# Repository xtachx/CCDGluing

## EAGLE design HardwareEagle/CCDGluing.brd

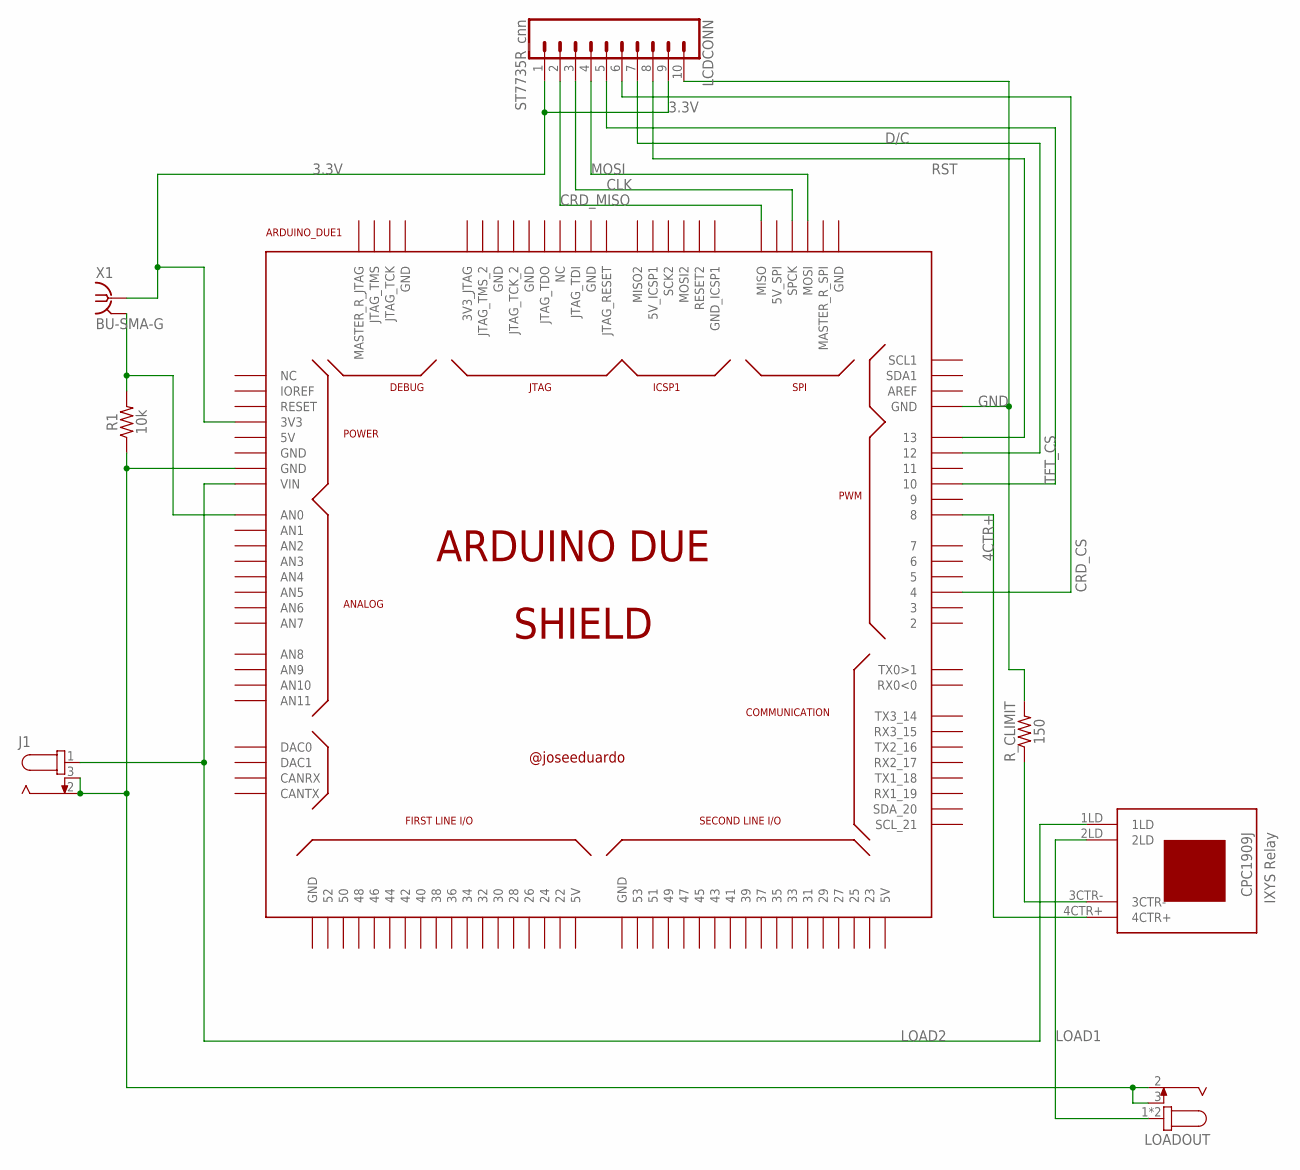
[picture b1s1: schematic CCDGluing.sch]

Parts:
ARDUINO_DUE1: ARDUINO_DUE_SHIELD
J1: 694106105102; 69410X105102
K1: CPC1909J
LCDCONN: ST7735R_cnn; 1X10
LOADOUT: 694103107102; 69410X107102
R1: 10k; 0603
R_CLIMIT: 150; 0603
X1: BU-SMA-G

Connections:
3.3V: ARDUINO_DUE1.3V3, LCDCONN.1, LCDCONN.9, X1.1
4CTR+: ARDUINO_DUE1.8, K1.4CTR+
CLK: ARDUINO_DUE1.SPCK, LCDCONN.3
CRD_CS: ARDUINO_DUE1.4, LCDCONN.6
CRD_MISO: ARDUINO_DUE1.MISO, LCDCONN.2
D/C: ARDUINO_DUE1.12, LCDCONN.7
GND: ARDUINO_DUE1.GND_4 (GND), LCDCONN.10, R_CLIMIT.2
LOAD1: K1.2LD, LOADOUT.1, LOADOUT.A1 (1)
LOAD2: ARDUINO_DUE1.VIN, J1.1, K1.1LD
LOAD_GND: ARDUINO_DUE1.GND_1 (GND), J1.2, J1.3, LOADOUT.2, LOADOUT.3, R1.1
MOSI: ARDUINO_DUE1.MOSI, LCDCONN.4
unnamed: K1.3CTR-, R_CLIMIT.1
unnamed: ARDUINO_DUE1.A0 (AN0), R1.2, X1.2, X1.3 (2), X1.4 (2), X1.5 (2)
RST: ARDUINO_DUE1.13, LCDCONN.8
TFT_CS: ARDUINO_DUE1.10, LCDCONN.5

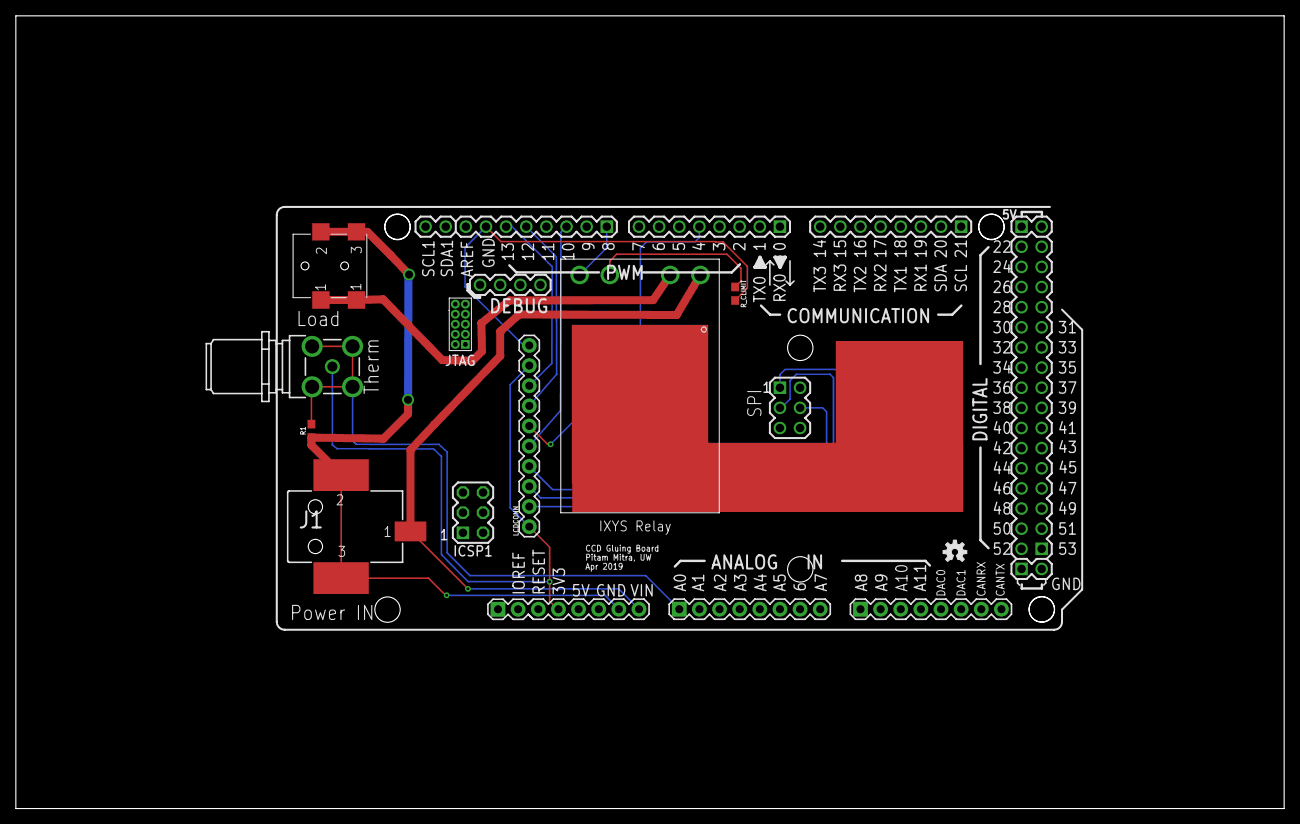
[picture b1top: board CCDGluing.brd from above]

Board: 2 copper layers, 160.0 x 100.0 mm, 9 parts (0 on the bottom side), 15 nets.

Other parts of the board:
U$1: OSHW-LOGO-S

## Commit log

2019-04-24 Hardware design added - for a board in the Arduino due shield form factor with the relay, thermistor and connection for the LCD screen
2019-04-25 Fixed the design to use the correct SPI port on the due. Blame the documentation for being wrong.
2019-04-25 Added current limit resistor.
2019-05-07 Arduino Due control for the Epoxy curing routine added. Note: All Berkeleylab instructions have been followed for thermal cycles, but none of this was tested with skipper CCDsgit add .gitignore Contr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
2019-05-24 Changed PID parameters. Fixed a bug with the output limits of the PID controller. State switching from MaintainWarm->Warmup now happens only when delta T > 10 C.
2019-05-29 Fixed a bug with the logic where maintainwarm would change to cooldown and reset the timer. Improved PID constants. Fixed wrong PID limit setting.

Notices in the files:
parts and their libraries:
Wurth_Elektronik_Electromechanic_DC_Powe: Copyright: Würth Elektronik
SparkFun-Connectors: Licensing: Creative Commons ShareAlike 4.0 International - https://creativecommons.org/licenses/by-sa/4.0
